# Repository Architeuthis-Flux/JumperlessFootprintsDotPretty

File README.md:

# 8.0
All my random KiCad footprints, symbols, and 3D models

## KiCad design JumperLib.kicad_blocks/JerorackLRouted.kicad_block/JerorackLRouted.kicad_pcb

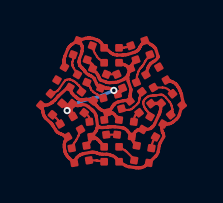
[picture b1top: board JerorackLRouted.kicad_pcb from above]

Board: 2 copper layers, 19 parts (0 on the bottom side), 20 nets.

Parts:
U1, U2, U3, U4, U5, U6, U7, U8, U9, U10, U11, U12, U13, U14, U15, U16, U17, U18, U19: XL-1010RGBC-WS2812B

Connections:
unnamed: U1.1 (DOUT), U2.4 (DIN)
unnamed: U1.2 (VDD), U2.2 (VDD), U3.2 (VDD), U4.2 (VDD), U5.2 (VDD), U6.2 (VDD), U7.2 (VDD), U8.2 (VDD), U9.2 (VDD), U10.2 (VDD), U11.2 (VDD), U12.2 (VDD), U13.2 (VDD), U14.2 (VDD), U15.2 (VDD), U16.2 (VDD), U17.2 (VDD), U18.2 (VDD), U19.2 (VDD)
unnamed: U1.3 (VSS), U2.3 (VSS), U3.3 (VSS), U4.3 (VSS), U5.3 (VSS), U6.3 (VSS), U7.3 (VSS), U8.3 (VSS), U9.3 (VSS), U10.3 (VSS), U11.3 (VSS), U12.3 (VSS), U13.3 (VSS), U14.3 (VSS), U15.3 (VSS), U16.3 (VSS), U17.3 (VSS), U18.3 (VSS), U19.3 (VSS)
unnamed: U2.1 (DOUT), U3.4 (DIN)
unnamed: U3.1 (DOUT), U4.4 (DIN)
unnamed: U4.1 (DOUT), U5.4 (DIN)
unnamed: U5.1 (DOUT), U6.4 (DIN)
unnamed: U6.1 (DOUT), U7.4 (DIN)
unnamed: U7.1 (DOUT), U8.4 (DIN)
unnamed: U8.1 (DOUT), U9.4 (DIN)
unnamed: U9.1 (DOUT), U10.4 (DIN)
unnamed: U10.1 (DOUT), U11.4 (DIN)
unnamed: U11.1 (DOUT), U12.4 (DIN)
unnamed: U12.1 (DOUT), U13.4 (DIN)
unnamed: U13.1 (DOUT), U14.4 (DIN)
unnamed: U14.1 (DOUT), U15.4 (DIN)
unnamed: U15.1 (DOUT), U16.4 (DIN)
unnamed: U16.1 (DOUT), U17.4 (DIN)
unnamed: U17.1 (DOUT), U18.4 (DIN)
unnamed: U18.1 (DOUT), U19.4 (DIN)

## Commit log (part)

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2026-03-12 init
2026-03-16 Add some more universalish footprints and some ridiculously specific ones
2026-04-08 add sspc and update knob
